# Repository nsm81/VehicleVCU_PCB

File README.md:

# VehicleVCU - 3 CANBUSs
The VehicleVCU provides three CANBUS transceivers for communication within a vehicle. An ESP32-S2FH4 microcontroller is utilised which has 4kB of flash and one CAN controller. For the other two CANBUSs, two exteral SPI CAN controllers are utilised.

## PCB & Enclosure

## Block Diagram

## MCU IO
| Description  | IO |
| ------------- | ------------- |
| Button 1 | IO4 |
| Button 2 | IO3 |
| Button 3 | IO2 |
| STATUS LED 1 | IO38 |
| STATUS LED 2 | IO37 |
| CAN1RX | IO34 |
| CAN1TX | IO35 |
| CAN1_INT | IO36 |
| CAN2_CS | IO21 |
| CAN2_SPI_INT | IO33 |
| CAN3_CS | IO9 |
| CAN3_SPI_INT | IO10 |
| MISO | IO31 |
| MOSI | IO32 |
| SCLK | IO30 |

## DTM PinOut
| Pin  | Description |
| ------------- | ------------- |
| 1 | GLV+ |
| 2 | CAN3L |
| 3 | CAN2L |
| 4 | CAN1L |
| 5 | CAN1H |
| 6 | CAN2H |
| 7 | CAN3H |
| 8 | GND |

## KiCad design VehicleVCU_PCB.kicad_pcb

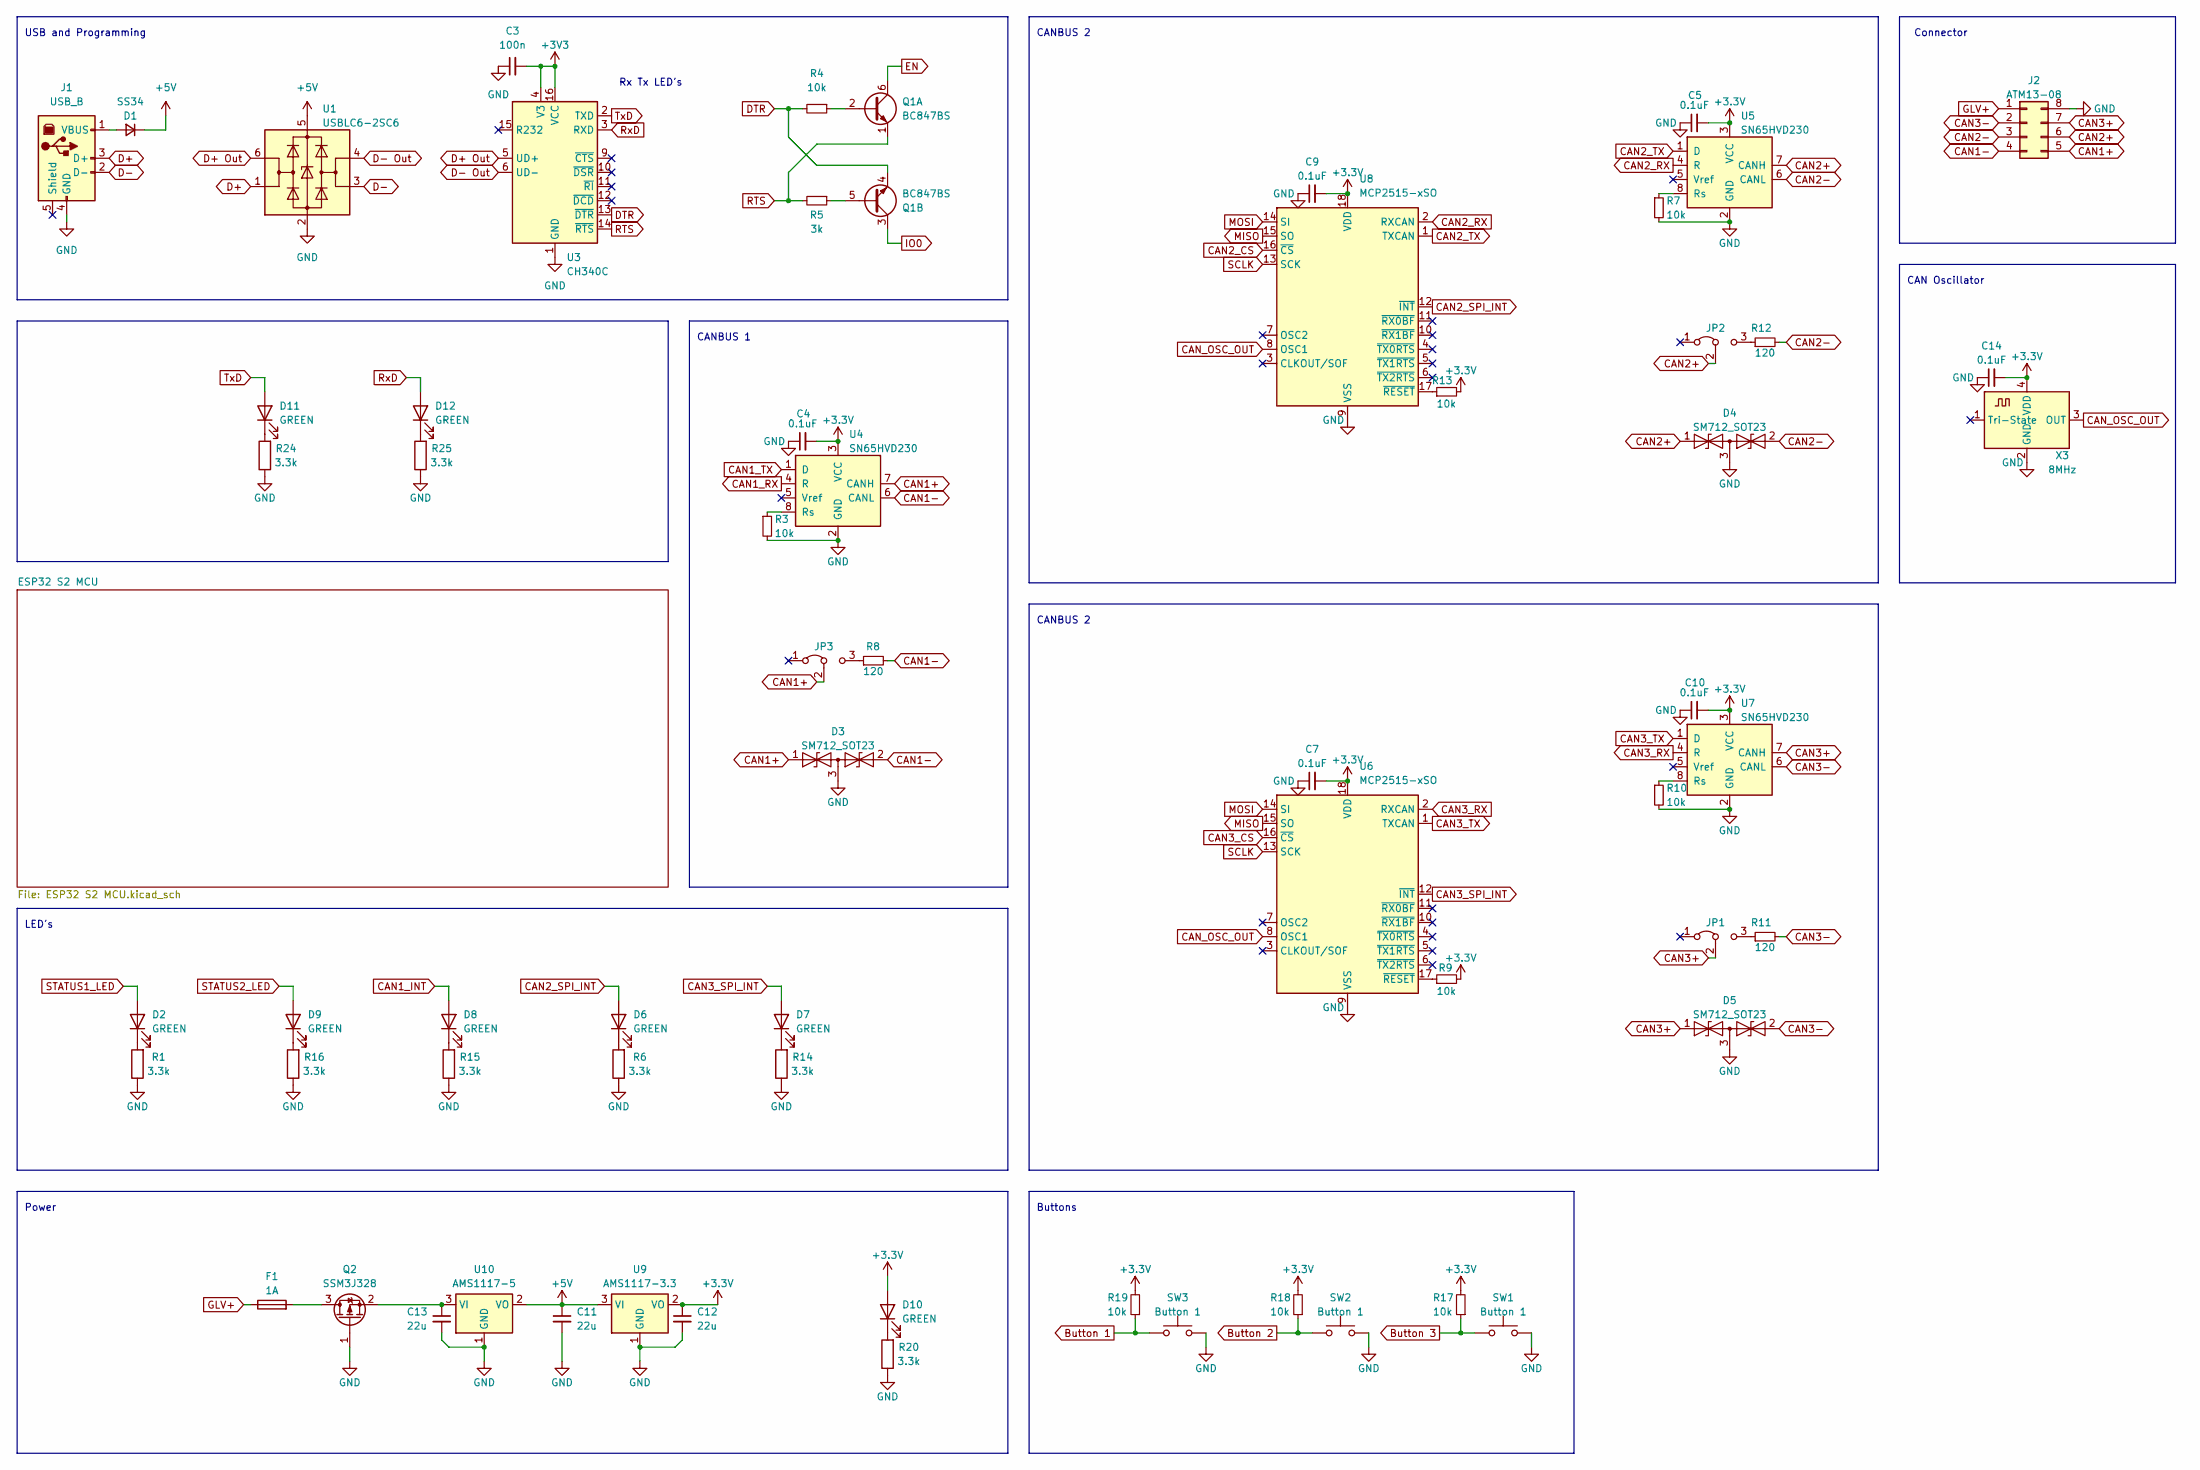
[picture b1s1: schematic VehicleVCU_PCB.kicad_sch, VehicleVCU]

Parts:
C3: 100n; C_0603_1608Metric
C4, C5, C7, C9, C10, C14: 0.1uF; C_0603_1608Metric
C11, C12, C13: 22u; C_0603_1608Metric
D1: SS34; D_SMA
D2, D6, D7, D8, D9, D10, D11, D12: GREEN; LED_0603_1608Metric; LCSC C72043
D3, D4, D5: SM712_SOT23; SOT-23
F1: 1A; Fuse_1206_3216Metric
J1: USB_B; USB_B_Lumberg_2411_02_Horizontal
J2: ATM13-08; ATM15-08
JP1, JP2, JP3: Jumper_2_Open; PinHeader_1x03_P2.54mm_Vertical
Q1: BC847BS; SOT-363_SC-70-6
Q2: SSM3J328; SOT-23-3
R1, R6, R14, R15, R16, R20, R24, R25: 3.3k; R_0603_1608Metric
R3, R4, R7, R9, R10, R13, R17, R18, R19: 10k; R_0603_1608Metric
R5: 3k; R_0603_1608Metric
R8, R11, R12: 120; R_0603_1608Metric
SW1, SW2, SW3: Button 1; SW_SPST_B3S-1000
U1: USBLC6-2SC6; SOT-23-6
U3: CH340C; SOIC-16_3.9x9.9mm_P1.27mm
U4, U5, U7: SN65HVD230; SOIC-8_3.9x4.9mm_P1.27mm; LCSC C12084
U6, U8: MCP2515-xSO; SOIC-18W_7.5x11.6mm_P1.27mm; LCSC C12368
U9: AMS1117-3.3; SOT-223-3_TabPin2
U10: AMS1117-5; SOT-223-3_TabPin2
X3: 8MHz; Oscillator_SMD_Abracon_ASE-4Pin_3.2x2.5mm; LCSC C717687

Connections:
+5V: C11.1, D1.1 (K), U1.5 (VBUS), U9.3 (VI), U10.2 (VO)
Button 1: R19.1, SW3.1; also elsewhere on the board
Button 2: R18.1, SW2.1; also elsewhere on the board
Button 3: R17.1, SW1.1; also elsewhere on the board
CAN1+: D3.1 (A1), J2.5, JP3.2 (C), U4.7 (CANH)
CAN1-: D3.2 (A2), J2.4, R8.2, U4.6 (CANL)
CAN1_INT: D8.2 (A); also elsewhere on the board
CAN1_RX: U4.4 (R); also elsewhere on the board
CAN1_TX: U4.1 (D); also elsewhere on the board
CAN2+: D4.1 (A1), J2.6, JP2.2 (C), U5.7 (CANH)
CAN2-: D4.2 (A2), J2.3, R12.2, U5.6 (CANL)
CAN2_CS: U8.16 (~CS); also elsewhere on the board
CAN2_RX: U5.4 (R), U8.2 (RXCAN)
CAN2_SPI_INT: D6.2 (A), U8.12 (~INT); also elsewhere on the board
CAN2_TX: U5.1 (D), U8.1 (TXCAN)
CAN3+: D5.1 (A1), J2.7, JP1.2 (C), U7.7 (CANH)
CAN3-: D5.2 (A2), J2.2, R11.2, U7.6 (CANL)
CAN3_CS: U6.16 (~CS); also elsewhere on the board
CAN3_RX: U6.2 (RXCAN), U7.4 (R)
CAN3_SPI_INT: D7.2 (A), U6.12 (~INT); also elsewhere on the board
CAN3_TX: U6.1 (TXCAN), U7.1 (D)
D+: J1.3 (D+), U1.1 (I/O1)
D+ Out: U1.6 (I/O1), U3.5 (UD+)
D-: J1.2 (D-), U1.3 (I/O2)
D- Out: U1.4 (I/O2), U3.6 (UD-)
DTR: Q1.4 (E2), R4.2, U3.13 (~DTR)
EN: Q1.6 (C1); also elsewhere on the board
GLV+: F1.1, J2.1
GND: C3.1, C4.1, C5.1, C7.1, C9.1, C10.1, C11.2, C12.2, C13.2, C14.1, D3.3 (common), D4.3 (common), D5.3 (common), J1.4 (GND), J2.8, Q2.1 (G), R1.1, R3.2, R6.1, R7.2, R10.2, R14.1, R15.1, R16.1, R20.1, R24.1, R25.1, SW1.2, SW2.2, SW3.2, U1.2 (GND), U3.1 (GND), U4.2 (GND), U5.2 (GND), U6.9 (VSS), U7.2 (GND), U8.9 (VSS), U9.1 (GND), U10.1 (GND), X3.2 (GND); also elsewhere on the board
IO0: Q1.3 (C2); also elsewhere on the board
MISO: U6.15 (SO), U8.15 (SO); also elsewhere on the board
MOSI: U6.14 (SI), U8.14 (SI); also elsewhere on the board
unnamed: D1.2 (A), J1.1 (VBUS)
unnamed: D2.1 (K), R1.2
unnamed: D6.1 (K), R6.2
unnamed: D7.1 (K), R14.2
unnamed: D8.1 (K), R15.2
unnamed: D9.1 (K), R16.2
unnamed: D10.1 (K), R20.2
unnamed: D11.1 (K), R24.2
unnamed: D12.1 (K), R25.2
unnamed: JP1.3 (B), R11.1
unnamed: JP2.3 (B), R12.1
unnamed: JP3.3 (B), R8.1
unnamed: Q1.2 (B1), R4.1
unnamed: Q1.5 (B2), R5.1
unnamed: F1.2, Q2.3 (D)
unnamed: C13.1, Q2.2 (S), U10.3 (VI)
unnamed: R3.1, U4.8 (Rs)
unnamed: R7.1, U5.8 (Rs)
unnamed: R9.1, U6.17 (~RESET)
unnamed: R10.1, U7.8 (Rs)
unnamed: R13.1, U8.17 (~RESET)
RTS: Q1.1 (E1), R5.2, U3.14 (~RTS)
RxD: D12.2 (A), U3.3 (RXD); also elsewhere on the board
SCLK: U6.13 (SCK), U8.13 (SCK); also elsewhere on the board
STATUS1_LED: D2.2 (A); also elsewhere on the board
STATUS2_LED: D9.2 (A); also elsewhere on the board
TxD: D11.2 (A), U3.2 (TXD); also elsewhere on the board

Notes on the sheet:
CAN Oscillator
Power
Connector
Buttons
Rx Tx LED's
LED's
CANBUS 2
USB and Programming
CANBUS 1

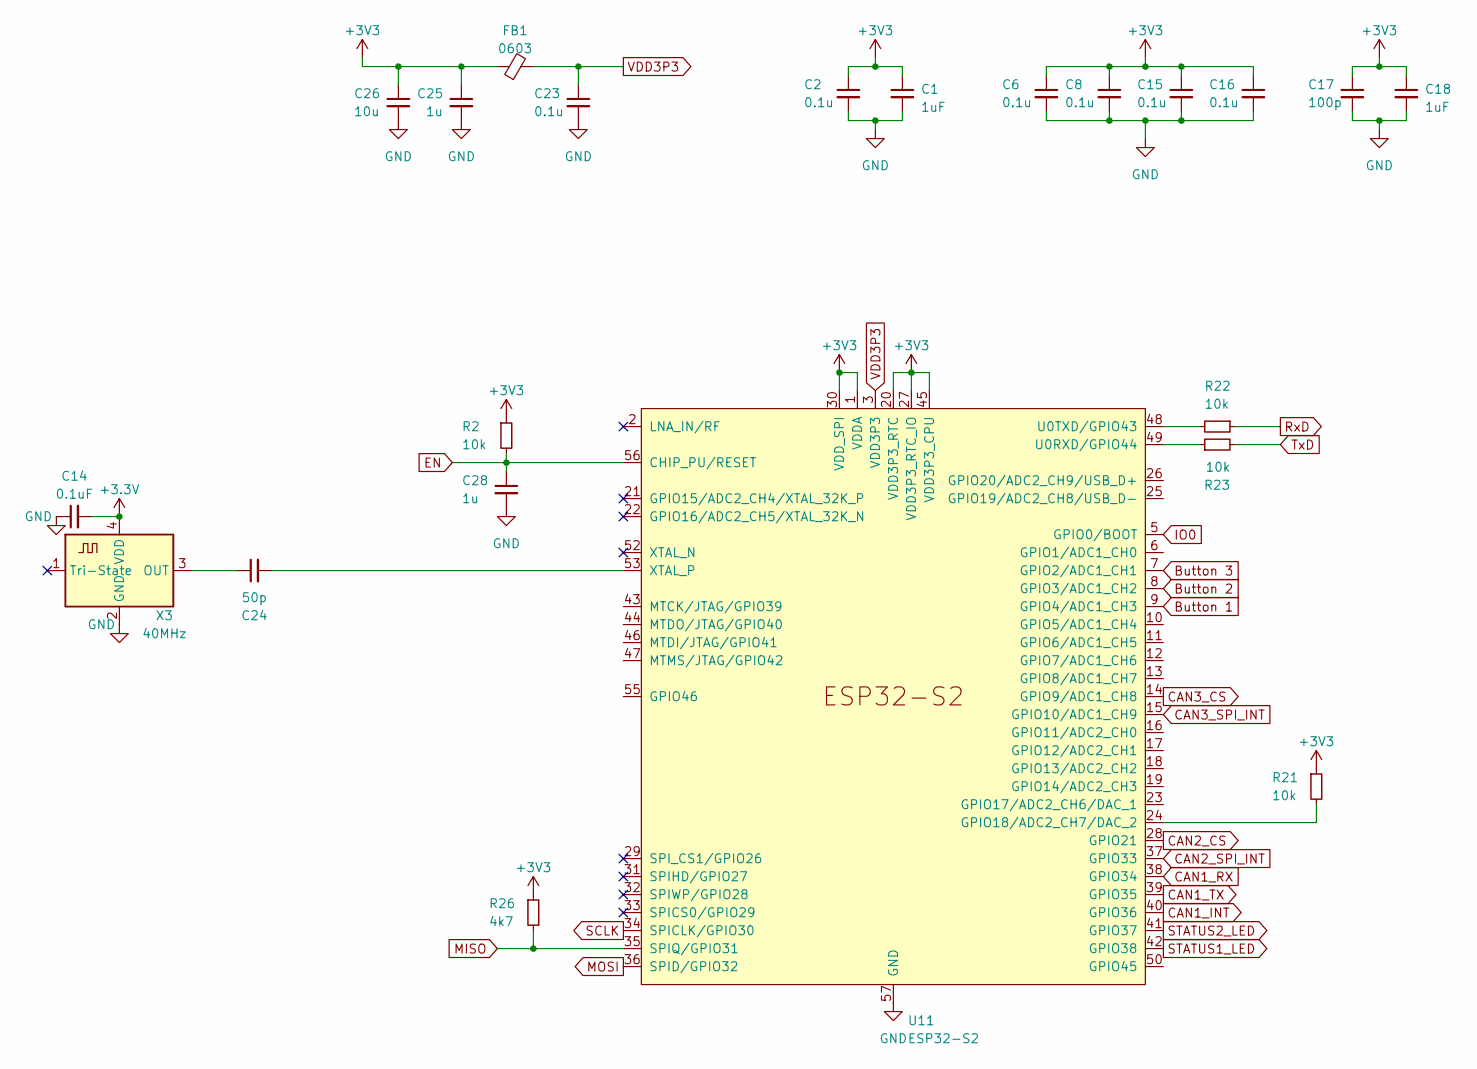
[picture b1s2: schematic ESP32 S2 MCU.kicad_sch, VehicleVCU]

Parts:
C1, C18: 1uF; C_0603_1608Metric
C2, C6, C8, C15, C16, C23: 0.1u; C_0603_1608Metric
C14: 0.1uF; C_0603_1608Metric
C17: 100p; C_0603_1608Metric
C24: 50p; C_0603_1608Metric
C25, C28: 1u; C_0603_1608Metric
C26: 10u; C_0603_1608Metric
FB1: 0603; L_0603_1608Metric
R2, R21, R22, R23: 10k; R_0603_1608Metric
R26: 4k7; R_0603_1608Metric
U11: ESP32-S2; QFN-56-1EP_7x7mm_P0.4mm_EP5.6x5.6mm
X3: 40MHz; Oscillator_SMD_Abracon_ASDMB-4Pin_2.5x2.0mm; LCSC C717687

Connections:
EN: C28.1, R2.2; also elsewhere on the board
GND: C1.2, C2.2, C6.2, C8.2, C14.1, C15.2, C16.2, C17.2, C18.2, C23.2, C25.2, C26.2, C28.2, X3.2 (GND); also elsewhere on the board
MISO: R26.2; also elsewhere on the board
unnamed 48: R21.2; also elsewhere on the board
unnamed 49: R23.1; also elsewhere on the board
unnamed 50: R22.2; also elsewhere on the board
unnamed 51: C24.2; also elsewhere on the board
RxD: R22.1; also elsewhere on the board
TxD: R23.2; also elsewhere on the board
VDD3P3: C23.1, FB1.2; also elsewhere on the board

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
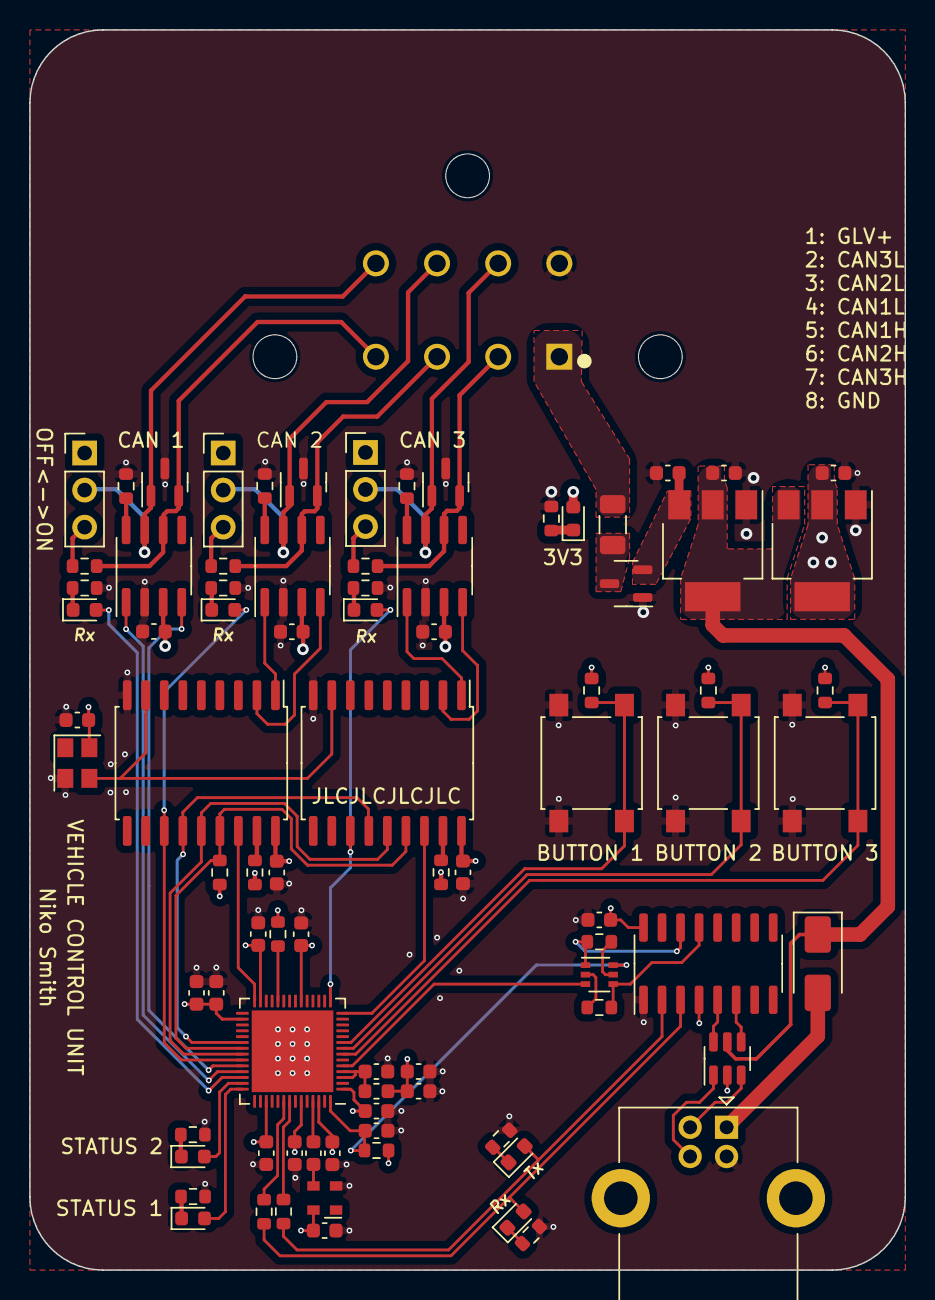
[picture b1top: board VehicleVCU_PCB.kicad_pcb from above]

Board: 4 copper layers, 60.0 x 85.0 mm, 86 parts (0 on the bottom side), 67 nets.

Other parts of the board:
C27: 0.1uF; C_0603_1608Metric
U2: ESP32-S2; QFN-56-1EP_7x7mm_P0.4mm_EP5.6x5.6mm
X1: 40MHz; Oscillator_SMD_Abracon_ASDMB-4Pin_2.5x2.0mm

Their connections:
Button 1: U2.9 (GPIO4/ADC1_CH3); also elsewhere on the board
Button 2: U2.8 (GPIO3/ADC1_CH2); also elsewhere on the board
Button 3: U2.7 (GPIO2/ADC1_CH1); also elsewhere on the board
CAN1_INT: U2.40 (GPIO36); also elsewhere on the board
CAN1_RX: U2.38 (GPIO34); also elsewhere on the board
CAN1_TX: U2.39 (GPIO35); also elsewhere on the board
CAN2_CS: U2.28 (GPIO21); also elsewhere on the board
CAN2_SPI_INT: U2.37 (GPIO33); also elsewhere on the board
CAN3_CS: U2.14 (GPIO9/ADC1_CH8); also elsewhere on the board
CAN3_SPI_INT: U2.15 (GPIO10/ADC1_CH9); also elsewhere on the board
EN: U2.56 (CHIP_PU/RESET); also elsewhere on the board
GND: C27.1, U2.57 (GND), X1.2 (GND); also elsewhere on the board
IO0: U2.5 (GPIO0/BOOT); also elsewhere on the board
MISO: U2.35 (SPIQ/GPIO31); also elsewhere on the board
MOSI: U2.36 (SPID/GPIO32); also elsewhere on the board
unnamed 48: U2.24 (GPIO18/ADC2_CH7/DAC_2); also elsewhere on the board
unnamed 49: U2.49 (U0RXD/GPIO44); also elsewhere on the board
unnamed 50: U2.48 (U0TXD/GPIO43); also elsewhere on the board
unnamed 51: U2.53 (XTAL_P); also elsewhere on the board
SCLK: U2.34 (SPICLK/GPIO30); also elsewhere on the board
STATUS1_LED: U2.42 (GPIO38); also elsewhere on the board
STATUS2_LED: U2.41 (GPIO37); also elsewhere on the board
VDD3P3: U2.3 (VDD3P3), U2.4 (VDD3P3); also elsewhere on the board

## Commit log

2023-06-25 Created Production Files and Added Rendering. Just need to add silkscreen of pinout
2023-06-25 Added Pinout and Block Diagram
2023-06-25 Final Commit. Created ibom
2023-06-25 Added images folder
2023-06-25 Renamed images
2023-06-25 Cropped Image
2023-06-25 Readme
2023-06-27 Submitted for Manufacturing
